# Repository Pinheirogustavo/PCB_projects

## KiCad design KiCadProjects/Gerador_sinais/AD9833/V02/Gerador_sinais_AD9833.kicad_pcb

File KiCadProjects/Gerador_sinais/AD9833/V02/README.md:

# Gerador de Sinais

## Descrição Geral do projeto

Sistema que gera um sinal senoidal com controle de amplitude e frequência.

Estágios: Gerador de sinais ( CA@300mV + DC) &rarr; Filtro  passa-alta &rarr; SinA (CA@300mV) &rarr; buffer &rarr;  amplificador não-inversor &rarr; Sin1(CA@300mV-3V).

## Componentes do circuito:

- Arduino nano: controlador do sistema
- AD9833: gerador de sinais confeccionado em módulo. Gera uma onda senoidal de amplitude fixa de 300mA e offset
- Ad828: Amplificador operacional dedicado ao ganho de sinal. 
	>Amplificador 1 é buffer entre o filtro passa-alta e o circuito de ganho.
	>Amplificador 2 é um amplificador não inversor. Vout = (1+pot/R2)*Vin
- X9c10x: potenciometro digital dedicado ao ganho de sinal

## Cuidados a serem tomados

Para a comunicação SPI, o dispositivo a ser controlado (Chip Select) é selecionado quando o respectivo pino CS está em LOW. Nunca pode-se permitir que dois dispositivos estejam com CS em LOW ao mesmo tempo. Por isso, no programa é preciso garantir que as operações com o AD9833 (select_wave, freq+ e freq-)  após um delay tragam o sinal do CS(AD9833) para LOW e depois devolvam para HIGH. E que as operações com o X9110X (aumento de R, redução de R, guardar R) após um delay tragam o sinal do CS(X9c10X) para LOW e depois devolvam para HIGH.

Assim, primeiramente o programa deve liberar o AD9833 (gerador de sinais) para ocupar a comunicação SPI, após a geração de sinal, desligar sua comunicação (trazer seu CS para HIGH) e liberar a comunicação SPI para ser requisitada a partir dos botões referentes a cada dispositivo. 

## Estágios do circuito

#### Entradas e saídas digitais do arduino nano:

>D2:  cs (X9X104) - Saída digital. Sinal de Chip Select do potenciômetro digital - "The device is selected when the CS input is LOW." 

>D3: storage_R - Usado para armazenar o valor de resistência - Botão 4 - Pressionar o botão faz o sinal X9c10x_INC  ficar em HIGH e o sinal  cs(X9X104) passar de HIGH para LOW e retornar a HIGH

>D4:  cs (AD9833) - Sinal de Chip Select do gerador de sinais

>D5:  Up_pot - Aumenta a resistência do potenciômetro (aumenta o ganho do sistema) - Botão 5 - Pressionar o botão faz com que o sinal de cs(X9X104) passe de HIGH para LOW, que o sinal X9c10x_INC altere de HIGH para LOW e o sinal  X9c10x_U/D fique em HIGH. Ao liberar o botão, o sinal de cs(X9X104) deve retornar para HIGH.
	 
>D6:  Down_pot - Reduz a resistência do potenciômetro (reduz o ganho do sistema) - Botão 6 - Pressionar o botão faz com que o sinal de cs(X9X104) passe de HIGH para LOW, X9c10x_INC altere de HIGH para LOW e o sinal  X9c10x_U/D fique em LOW. Ao liberar o botão, o sinal de cs(X9X104) deve retornar para HIGH.

>D7:  X9c10x_INC - Saída digital. Responsável pelo disparo do sinal que habilita o incremento e o decremento da resistência. Alterado pelos sinais em Up_pot/Down_pot.

>D8:  X9c10x_U/D -  Saída digital. Responsável pela seleção do sinal de incremento ou decremento da resistência. Controlado pelos sinais em Up_pot/Down_pot.

>D9:  freq+   - Incrementa a frequência do sinal (a definir o tamanho do incremento) - Botão 2 - Ainda não implementado no programa.

>D10: freq-   - Decrementa a frequência do sinal (a definir o tamanho do decremento) - Botão 3 - Ainda não implementado no programa.

>D11: SPI_COPI - Saída digital. Sinal de controle do arduino para a entrada SDATA do gerador de sinais.

>D12: S_wave - Seleciona a forma de onda desejada (seno, triangular ou quadrada) - Botão 1 - Ainda não implementado no programa.

>D13: SPI_clk - Saída digital. Sinal de clock entre o arduino e o gerador de sinais

#### O potenciômetro digital

- Programa baseado em: https://www.electroniclinic.com/digital-potentiometer-x9c103s-arduino-circuit-and-programming/

- Pin Descriptions - X9c10x:

#### O Gerador de sinais

- Programa baseado em: https://www.electroniclinic.com/ad9833-programmable-waveform-generator-using-arduino/
- Biblioteca necessária: https://github.com/Billwilliams1952/AD9833-Library-Arduino

## Esquemático

## PCB

## PCB-3D

## PCB Máscara

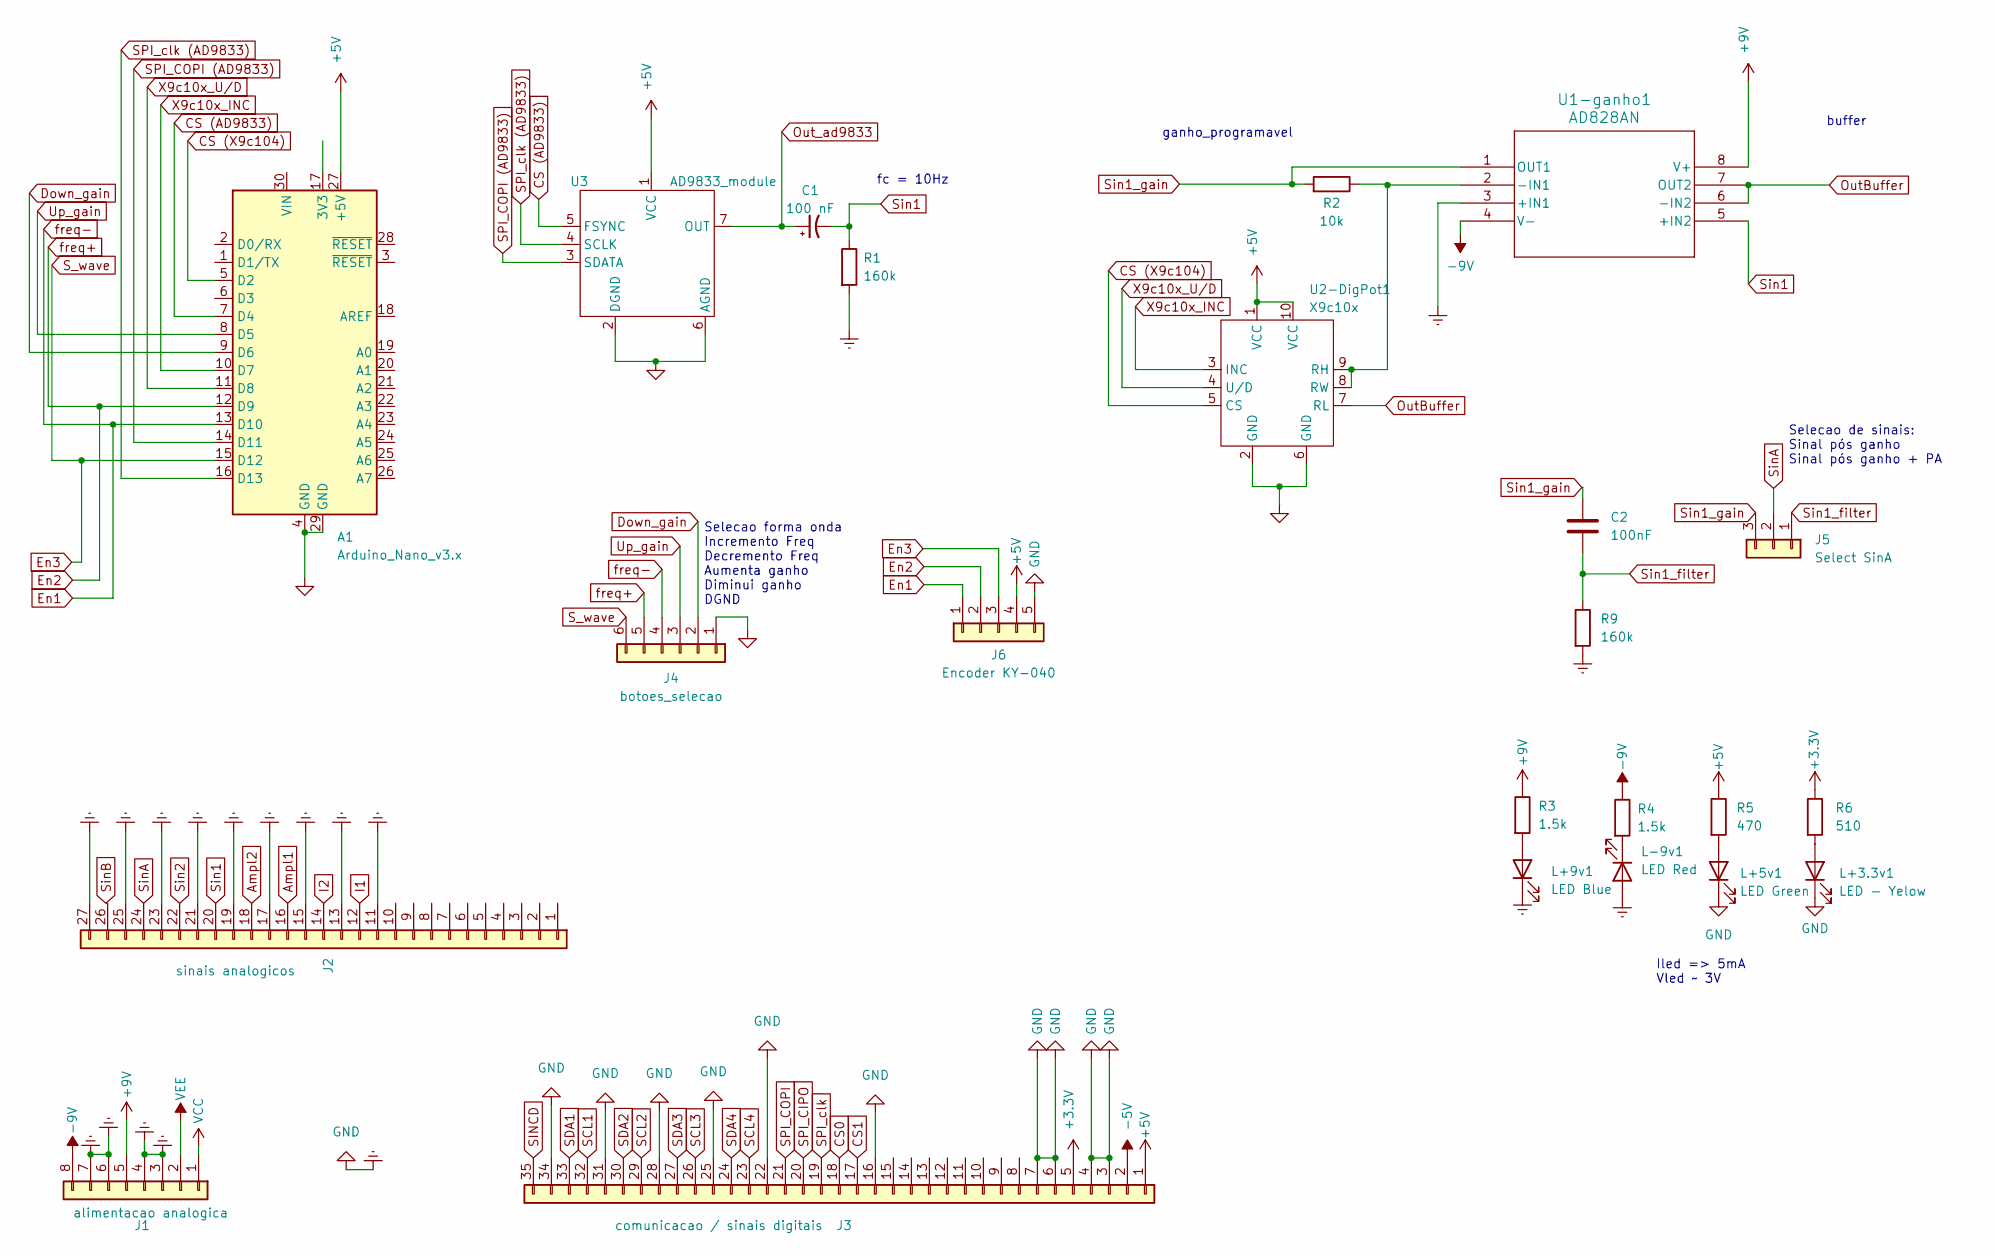
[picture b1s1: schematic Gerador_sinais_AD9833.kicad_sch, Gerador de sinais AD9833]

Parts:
A1: Arduino_Nano_v3.x; Arduino_Nano
C1: 100 nF; CP_Radial_D5.0mm_P2.50mm
C2: 100nF; C_Disc_D3.0mm_W1.6mm_P2.50mm
J1: alimentacao analogica; PinHeader_1x08_P2.54mm_Vertical
J2: sinais analogicos; PinHeader_1x27_P2.54mm_Vertical
J3: comunicacao / sinais digitais; PinHeader_1x35_P2.54mm_Vertical
J4: botoes_selecao; PinHeader_1x06_P2.54mm_Vertical
J5: Select SinA; PinHeader_1x03_P2.54mm_Vertical
J6: Encoder KY-040; PinHeader_1x05_P2.54mm_Vertical
L+3.3v1: LED - Yelow; LED_D5.0mm
L+5v1: LED Green; LED_D5.0mm
L+9v1: LED Blue; LED_D5.0mm
L-9v1: LED Red; LED_D5.0mm
R1: 160k; R_Axial_DIN0204_L3.6mm_D1.6mm_P5.08mm_Horizontal
R2: 10k; R_Axial_DIN0207_L6.3mm_D2.5mm_P7.62mm_Horizontal
R3, R4: 1.5k; R_Axial_DIN0207_L6.3mm_D2.5mm_P7.62mm_Horizontal
R5: 470; R_Axial_DIN0207_L6.3mm_D2.5mm_P7.62mm_Horizontal
R6: 510; R_Axial_DIN0207_L6.3mm_D2.5mm_P7.62mm_Horizontal
R9: 160k; R_Axial_DIN0207_L6.3mm_D2.5mm_P7.62mm_Horizontal
U1-ganho1: AD828AN; AD828
U2-DigPot1: X9c10x; X9c10X_module
U3: AD9833_module

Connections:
+3.3V: J3.5, R6.1
+5V: A1.27 (+5V), J3.1, J6.4, R5.1, U2-DigPot1.1 (VCC), U2-DigPot1.10 (VCC), U3.1 (VCC)
+9V: J1.5, R3.1, U1-ganho1.8 (V+)
-5V: J3.2
-9V: J1.8, R4.1, U1-ganho1.4 (V-)
Ampl1: J2.16
Ampl2: J2.18
CS0: J3.18
CS1: J3.17
CS (AD9833): A1.7 (D4), U3.5 (FSYNC)
CS (X9c104): A1.5 (D2), U2-DigPot1.5 (CS)
Down_gain: A1.9 (D6), J4.2
Earth: A1.4 (GND), A1.29 (GND), J1.3, J1.4, J1.6, J1.7, J2.11, J2.13, J2.15, J2.17, J2.19, J2.21, J2.23, J2.25, J2.27, J3.3, J3.4, J3.6, J3.7, J3.16, J3.22, J3.25, J3.28, J3.31, J3.34, J4.1, J6.5, L+3.3v1.1 (K), L+5v1.1 (K), L+9v1.1 (K), L-9v1.2 (A), R1.2, R9.2, U1-ganho1.3 (+IN1), U2-DigPot1.2 (GND), U2-DigPot1.6 (GND), U3.2 (DGND), U3.6 (AGND)
En1: A1.13 (D10), J4.4, J6.1
En2: A1.12 (D9), J4.5, J6.2
En3: A1.15 (D12), J4.6, J6.3
I1: J2.12
I2: J2.14
unnamed: L+3.3v1.2 (A), R6.2
unnamed: L+5v1.2 (A), R5.2
unnamed: L+9v1.2 (A), R3.2
unnamed: L-9v1.1 (K), R4.2
unnamed: R2.1, U1-ganho1.2 (-IN1), U2-DigPot1.8 (RW), U2-DigPot1.9 (RH)
OutBuffer: U1-ganho1.6 (-IN2), U1-ganho1.7 (OUT2), U2-DigPot1.7 (RL)
Out_ad9833: C1.1, U3.7 (OUT)
SCL1: J3.32
SCL2: J3.29
SCL3: J3.26
SCL4: J3.23
SDA1: J3.33
SDA2: J3.30
SDA3: J3.27
SDA4: J3.24
SINCD: J3.35
SPI_CIPO: J3.20
SPI_COPI: J3.21
SPI_COPI (AD9833): A1.14 (D11), U3.3 (SDATA)
SPI_clk: J3.19
SPI_clk (AD9833): A1.16 (D13), U3.4 (SCLK)
Sin1: C1.2, J2.20, R1.1, U1-ganho1.5 (+IN2)
Sin1_filter: C2.2, J5.1, R9.1
Sin1_gain: C2.1, J5.3, R2.2, U1-ganho1.1 (OUT1)
Sin2: J2.22
SinA: J2.24, J5.2
SinB: J2.26
Up_gain: A1.8 (D5), J4.3
VCC: J1.1
VEE: J1.2
X9c10x_INC: A1.10 (D7), U2-DigPot1.3 (INC)
X9c10x_U/D: A1.11 (D8), U2-DigPot1.4 (U/D)

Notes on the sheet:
ganho_programavel
Selecao forma onda Incremento Freq Decremento Freq Aumenta ganho Diminui ganho DGND
Iled => 5mA Vled ~ 3V
Selecao de sinais: Sinal pós ganho Sinal pós ganho + PA
fc = 10Hz
buffer

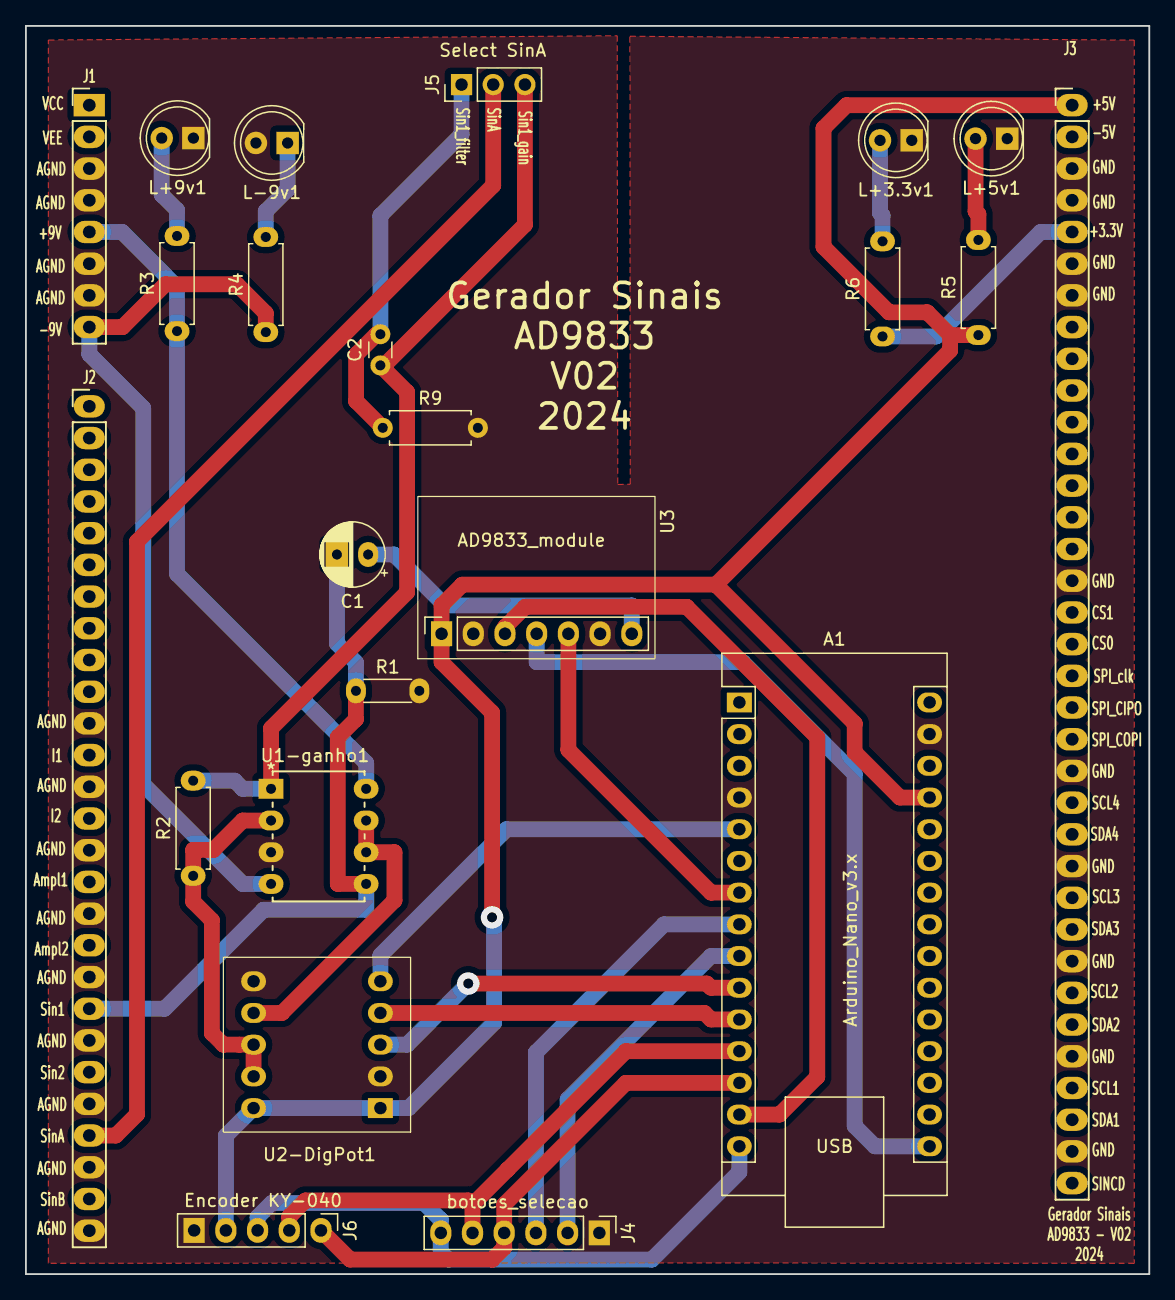
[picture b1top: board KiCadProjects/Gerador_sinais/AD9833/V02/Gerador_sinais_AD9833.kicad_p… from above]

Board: 2 copper layers, 90.0 x 100.0 mm, 23 parts (0 on the bottom side), 27 nets.

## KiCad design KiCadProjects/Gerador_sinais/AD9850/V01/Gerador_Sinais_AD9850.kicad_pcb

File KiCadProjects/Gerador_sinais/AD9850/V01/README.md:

# Gerador de Sinais

## Descrição Geral do projeto

O gerador de sinais é baseado no AD9850. São gerados dois sinais senoidais e dois sinais quadrados, com banda de frequência entre 1 Hz e 40 MHz.

 - Sinais Senoidais: Controle de amplitude e frequência;
 - Sinais quadrados: Controle de frquência.

## Descrição do sistema

#### Gerador de sinais AD9850

O gerador é controlado por quatro sinais digitais vindos do uC STM32. Sua alimentação é feita pelo barramento principal com 5V.

Os sinais quadrados SQ_AD1 e SQ_AD2 passam por um filtro passivo de primeira ordem passa alta, com frequência de corte de 10 Hz. Esses sinais ficam disponíveis na barra de pinos "Squad_wave" como SQ1 e SQ2.

Os sinais senoidais sin_AD1 e sin_AD2 passam por um filtro passivo de primeira ordem passa alta, com frequência de corte de 10 Hz. Esses sinais ficam disponíveis no barramento principal  como Sin1 e Sin2.

#### Circuito de ganho

Os sinais Sin1 e Sin2 entram em um Amplificador Inversor, com o resistor de entrada sendo um potenciômetro digital X9c10x e o resistor de feedback de 51k. O amplificador usado é o AD826/828. 

O controle de cada potenciômetro digital é feito por três sinais digitais vindos do uC STM32. Sua alimentação é feita pelo barramento principal com 5V.

Os sinais Sin1 e Sin2, após passarem por esse estágio de ganho, são nomeados por Sin1_gain e Sin2_gain, respectivamente.

#### Filtro pós ganho

Em simulações realizadas foi observado offset nos sinais após a realização do ganho. Por esse motivo, foi adicionado um estágio, opcional, de filtro Passa-Alta e buffer. Os sinais Sin1_gain e Sin2_gain entram nesse estágio e saem nomeados como Sin1_filter e Sin2_filter

#### Seleção dos sinais para SinA e SinB

O barramento principal do Eitduino recebe os sinais SinA e SinB. Estes podem ser selecionados a partir de  Sin_gain ou Sin_filter por meio de pinos "Select_SinA" e "Select_sinB".

#### Opções de controle por entradas digitais

###### Botões

Quatro botões podem ser implementados para controle de frequência e amplitude do sinal senoidal. Eles são conectados a entradas digitais do uC STM32 (que devem ser definidas como pullup).

###### Teclado matricial

Um teclado matricial 4x4 pode ser implementado para realizar os controles de  frequência e amplitude do sinal senoidal. Esses modelos de teclados numéricos geralmente possuem resistores pullup internos.

###### Encoder

Um encoder pode ser implementado para realizar os controles de  frequência e amplitude do sinal senoidal, em conjunto com os sinais vindos dos botões ou do teclado matricial. Um modelo de fácil acesso é o KY-040, de 20 steps por revolução.

## Descrição do esquemático

###### A1 - Squad Wave

Componentes para filtrar e disponibilisar os dois sinais quadrados.

 > Os sinais quadrados que saem do AD9850, SQ_AD1 e SQ_AD2, passam por um filtro PA e saem como SQ1 e SQ2.
 > SQ1 e SQ2 ficam disponíveis em uma barra de pinos (Squad_wave) junto com o AGND.

###### A2 - Encoder

Barra de pinos (encoder ky-040) para encaixe do módulo encoder como o KY-040. 

 > O módulo encoder trabalha com cinco pinos. +5V e DNGD para alimentação. Os outros três pinos são sinais digitais (En1, En2 e En3) que enviam dados para o uC.
 
 As conexões entre o encoder e o uC são:
 
	En1       PA15
	En2       PB8
	En3       PB9

###### A3 - Teclado matricial

Barra de pinos (teclado matricial) para conexão do teclado matricial 4x4.

 > São oito pinos de sinais digitais (M1, M2, ... , M8) que enviam dados para o uC.

As conexões entre o teclado e o uC são:

	M1        PA2
	M2        PA3
	M3        PA12
	M4        PA11
	M5        PA6
	M6        PA7
	M7        PB0
	M8        PB12

###### A4 - botões

Barra de pinos (botoes_selecao) para conexão de 4 botões.

 > São quatro pinos para conexão de botões e um pino DGND. Os quatro pinos dos botões são:
 
	Freq +: incrementa a frequência dos sinais gerados
	Freq -: decrementa a frequência dos sinais gerados
	Up_gain: incrementa a amplitude dos sinais gerados
	Down_gain: decrementa a amplitude dos sinais gerados
    
As conexões entre os botoes e o uC são:

	Freq+         PB13
	Freq-         PB14
	Up_gain       PB15
	Down_gain     PA8
    
 > Os botões devem ser conectados ao sinal DGND presente na barra de pinos  e nas entradas digitais do uC. Essas entradas devem estar definidas com pullup. 

###### B1 - AD9850

Modelo de componente criado nas dimensões do módulo utilizado.

As conexões entre o módulo e o uC são:

	W_CLK     PC14
	FQ_UD     PC15
	DATA      PA0
	RESET     PA1
    
Os sinais senoidais (com offset) fornecidos são: sin_AD1 e sin_AD2

A alimentação é feita por: +5V e DGND

###### C1 - Filtro saída AD9850

###### B2 - uC STM32

Alimentação: pode ser feita por 3.3V ou 5.0V - jumper na barra de pinos (3.3V STM32 **OU** 5.0V STM32).

Entradas Digitais: Ver "Encoder", "Teclado matricial" e "Botões".

Saídas digitais: Ver "AD9850" e "DigPot1 / DigPot2" em "Ganho programável".

Entradas Analógicas:

	PA4       Ampl1 (amplitude da corrente I1 - vinda do barramento principal)
	PA5       Ampl2 (amplitude da corrente I2 - vinda do barramento principal)

Comunicação I2C: O uC está conectado ao barramento principal de comunicação I2C-1. No primeiro momento essa funcionalidade não é utilizada, mas foi implementada caso optemos por realizar o controle do sinal de excitação por outro uC de outro módulo do projeto. 
Há resistores pullup (+3.3V) para essa comunicação.

###### C1 e D1 - Barramento principal

Verificar os sinais dispo no barramento principal em: <https://github.com/Pinheirogustavo/PCB_projects>

###### C3 - LEDs de alimentação

LEDs de diferentes cores para indicar o correto fornecimento das tensões empregadas no circuito.

Foi considerado uma tensão de joelho de aproximadamente 3V e uma corrente de 5mA para ter o um brilho perceptível e baixo consumo de energia.

 - Azul:        +9V
 - Vermelho:    -9V
 - Verde:       +5V
 - Amarelo:     +3.3V

###### A5 e B5 - Ganho programável

Amplificador duplo (AD826/828) na forma não inversor para controle do ganho do sinal senoidal filtrado vindo do AD9850.

Cada um dos sinais (Sin1 e Sin2) passa por um potenciômetro digital diferente (DIgPot 1 e DigPot2). Ambos estão conectados à entrada não inversora do amplificador. 

Cada potenciômetro digital (DigPot) possui um vetor resistivo de 99 passos. O CI X9c104 possui resistência máxima de $100k \Omega$. Ele é controlado por 4 sinais digitais.

As conexões entre os potenciômetros digitais e o uC são:

	Pot1_CS_(X9c104)      PB1
	Pot1_X9c10x_U/D       PB10
	Pot1_X9c10x_INC       PB11

	Pot2_CS_(X9c104)      PB5
	Pot2_X9c10x_U/D       PB4 
	Pot2_X9c10x_INC       PB3 

###### C5 - Filtro e buffer

## Particularidades na construção da PCB

Devido o tamanho restrito da placa e o grande número de componentes, foram adotados tamanhos de trilha e espaçamentos diferentes dos padrões.

 - Tamanho de trilha: 0,50mm
 - Espaçamento: 0,50mm
 - Tamnho de via: 1,00mm furo da via: 0,60mm
 - Pads:
 	- Resistor: circular 1,6mm furo 0,8mm
 	- capacitor: oval 1,8x2,0mm furo 1,1mm
 	- Barra de pinos (excerto principais): oval 1,8x2,0mm furo 1,02mm
 	- AmpOp: circular 1,6mm furo 0,8mm

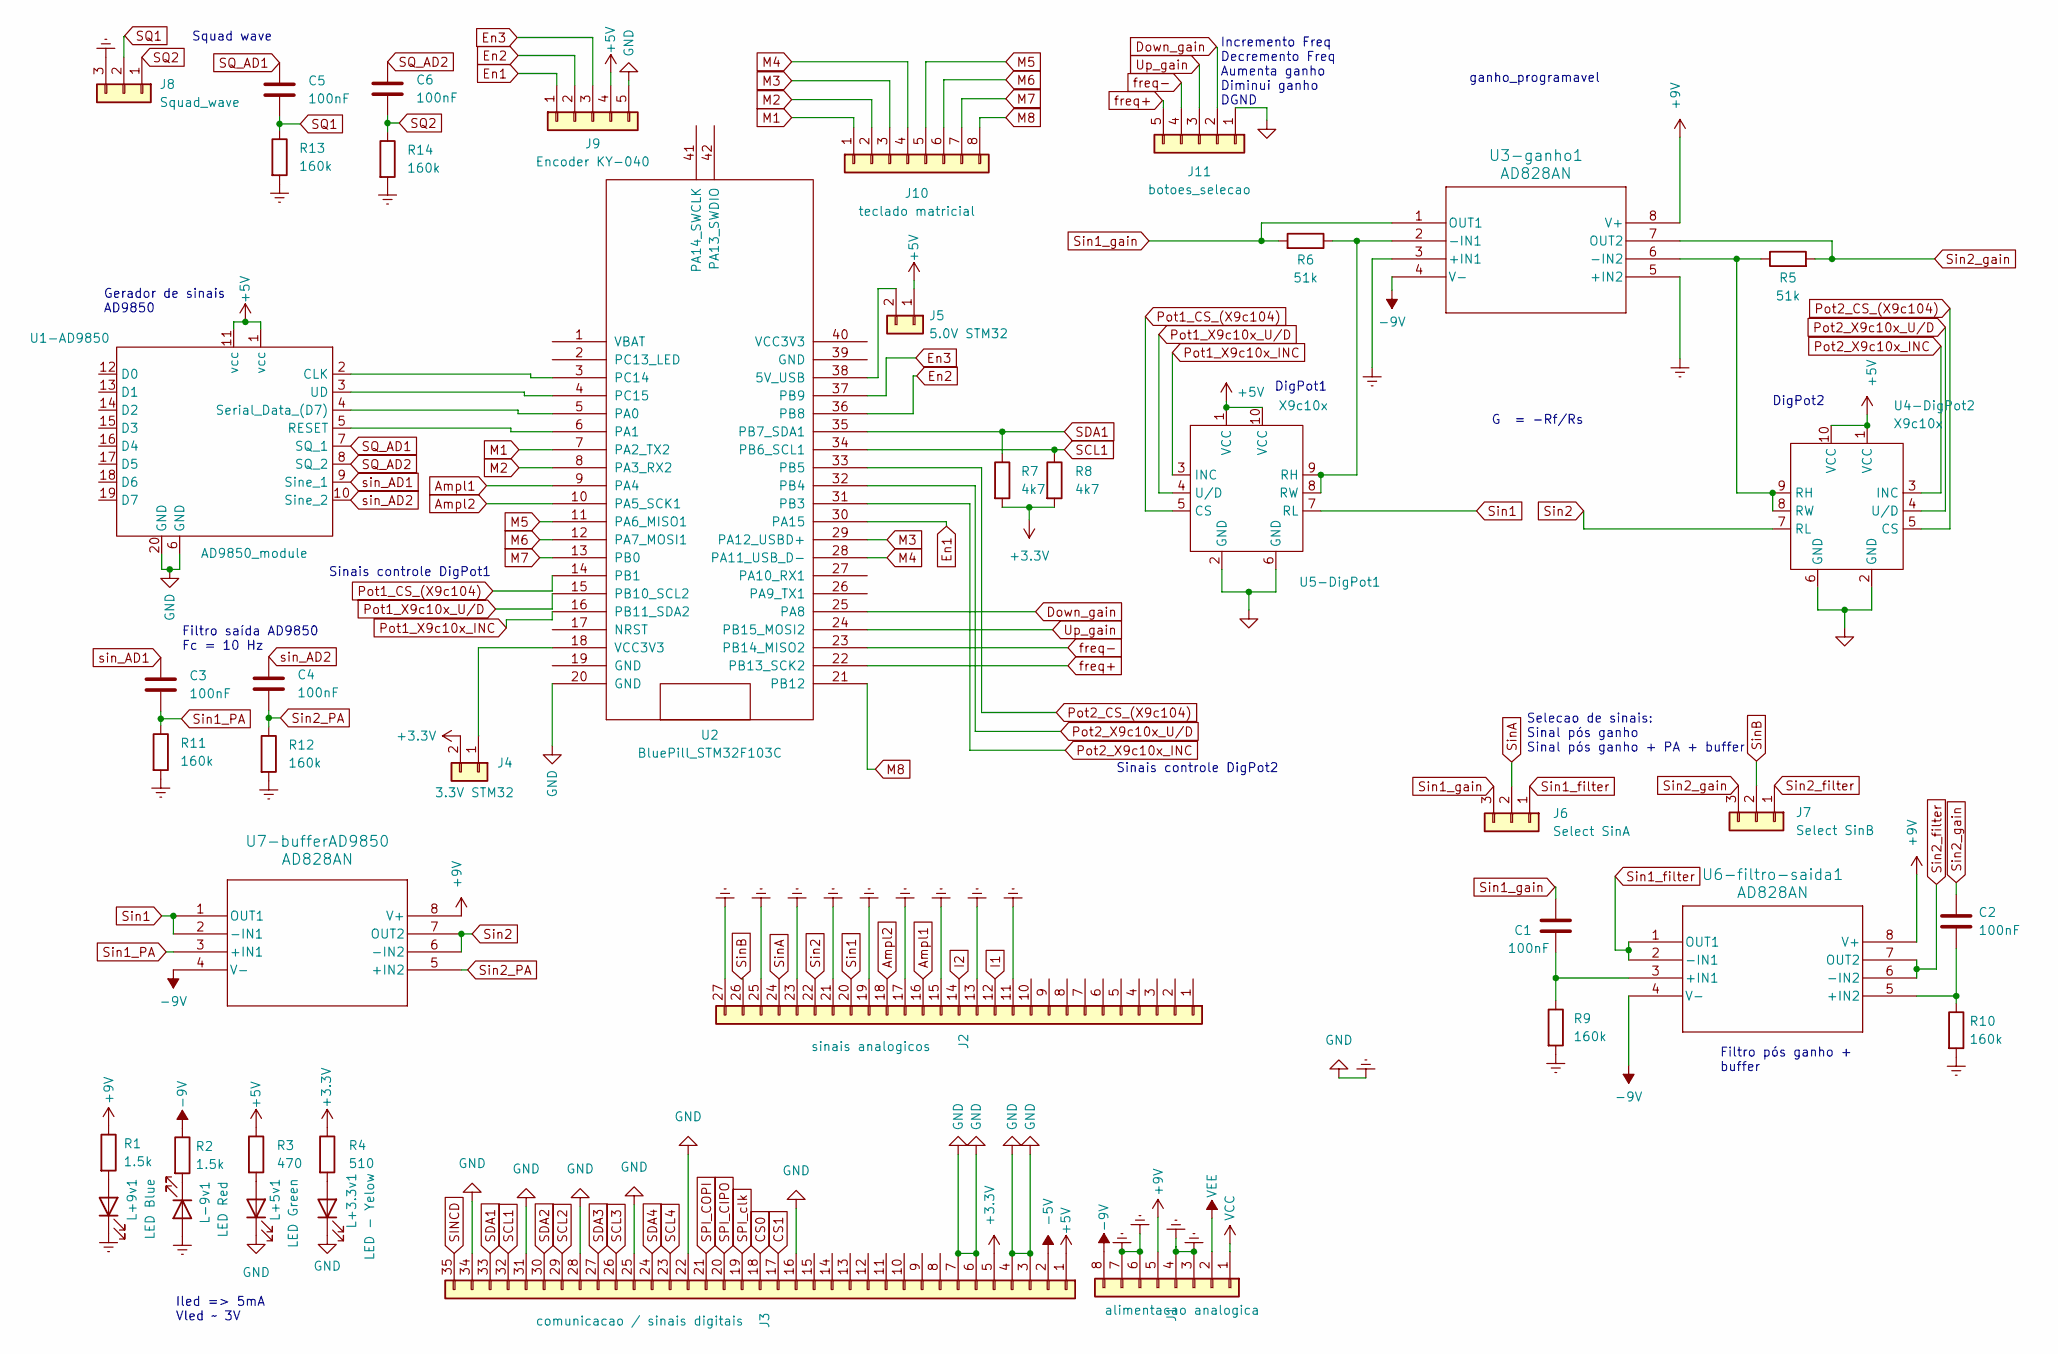
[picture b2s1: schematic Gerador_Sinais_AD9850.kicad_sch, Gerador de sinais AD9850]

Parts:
C1, C2, C3, C4, C5, C6: 100nF; C_Disc_D3.0mm_W1.6mm_P2.50mm
J1: alimentacao analogica; PinHeader_1x08_P2.54mm_Vertical
J2: sinais analogicos; PinHeader_1x27_P2.54mm_Vertical
J3: comunicacao / sinais digitais; PinHeader_1x35_P2.54mm_Vertical
J4: 3.3V STM32; PinHeader_1x02_P2.54mm_Vertical
J5: 5.0V STM32; PinHeader_1x02_P2.54mm_Vertical
J6: Select SinA; PinHeader_1x03_P2.54mm_Vertical
J7: Select SinB; PinHeader_1x03_P2.54mm_Vertical
J8: Squad_wave; PinHeader_1x03_P2.54mm_Vertical
J9: Encoder KY-040; PinHeader_1x05_P2.54mm_Vertical
J10: teclado matricial; PinHeader_1x08_P2.54mm_Horizontal
J11: botoes_selecao; PinHeader_1x05_P2.54mm_Horizontal
L+3.3v1: LED - Yelow; LED_D5.0mm
L+5v1: LED Green; LED_D5.0mm
L+9v1: LED Blue; LED_D5.0mm
L-9v1: LED Red; LED_D5.0mm
R1, R2: 1.5k; R_Axial_DIN0207_L6.3mm_D2.5mm_P7.62mm_Horizontal
R3: 470; R_Axial_DIN0207_L6.3mm_D2.5mm_P7.62mm_Horizontal
R4: 510; R_Axial_DIN0207_L6.3mm_D2.5mm_P7.62mm_Horizontal
R5, R6: 51k; R_Axial_DIN0207_L6.3mm_D2.5mm_P7.62mm_Horizontal
R7, R8: 4k7; R_Axial_DIN0207_L6.3mm_D2.5mm_P7.62mm_Horizontal
R9, R10, R11, R12, R13, R14: 160k; R_Axial_DIN0207_L6.3mm_D2.5mm_P7.62mm_Horizontal
U1-AD9850: AD9850_module
U2: BluePill_STM32F103C
U3-ganho1, U6-filtro-saida1, U7-bufferAD9850: AD828AN; AD828
U4-DigPot2, U5-DigPot1: X9c10x; X9c10X_module

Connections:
+3.3V: J3.5, J4.2, R4.1, R7.2, R8.2
+5V: J3.1, J5.1, J9.4, R3.1, U1-AD9850.1 (vcc), U1-AD9850.11 (vcc), U4-DigPot2.1 (VCC), U4-DigPot2.10 (VCC), U5-DigPot1.1 (VCC), U5-DigPot1.10 (VCC)
+9V: J1.5, R1.1, U3-ganho1.8 (V+), U6-filtro-saida1.8 (V+), U7-bufferAD9850.8 (V+)
-5V: J3.2
-9V: J1.8, R2.1, U3-ganho1.4 (V-), U6-filtro-saida1.4 (V-), U7-bufferAD9850.4 (V-)
Ampl1: J2.16, U2.9 (PA4)
Ampl2: J2.18, U2.10 (PA5_SCK1)
CS0: J3.18
CS1: J3.17
Down_gain: J11.2, U2.25 (PA8)
Earth: J1.3, J1.4, J1.6, J1.7, J2.11, J2.13, J2.15, J2.17, J2.19, J2.21, J2.23, J2.25, J2.27, J3.3, J3.4, J3.6, J3.7, J3.16, J3.22, J3.25, J3.28, J3.31, J3.34, J8.3, J9.5, J11.1, L+3.3v1.1 (K), L+5v1.1 (K), L+9v1.1 (K), L-9v1.2 (A), R9.2, R10.2, R11.2, R12.2, R13.2, R14.2, U1-AD9850.6 (GND), U1-AD9850.20 (GND), U2.20 (GND), U3-ganho1.3 (+IN1), U3-ganho1.5 (+IN2), U4-DigPot2.2 (GND), U4-DigPot2.6 (GND), U5-DigPot1.2 (GND), U5-DigPot1.6 (GND)
En1: J9.1, U2.30 (PA15)
En2: J9.2, U2.36 (PB8)
En3: J9.3, U2.37 (PB9)
I1: J2.12
I2: J2.14
M1: J10.1, U2.7 (PA2_TX2)
M2: J10.2, U2.8 (PA3_RX2)
M3: J10.3, U2.29 (PA12_USBD+)
M4: J10.4, U2.28 (PA11_USB_D-)
M5: J10.5, U2.11 (PA6_MISO1)
M6: J10.6, U2.12 (PA7_MOSI1)
M7: J10.7, U2.13 (PB0)
M8: J10.8, U2.21 (PB12)
unnamed: J4.1, U2.18 (VCC3V3)
unnamed: J5.2, U2.38 (5V_USB)
unnamed: L+3.3v1.2 (A), R4.2
unnamed: L+5v1.2 (A), R3.2
unnamed: L+9v1.2 (A), R1.2
unnamed: L-9v1.1 (K), R2.2
unnamed: U1-AD9850.2 (CLK), U2.3 (PC14)
unnamed: U1-AD9850.5 (RESET), U2.6 (PA1)
unnamed: U1-AD9850.4 (Serial_Data_(D7)), U2.5 (PA0)
unnamed: U1-AD9850.3 (UD), U2.4 (PC15)
unnamed: R6.1, U3-ganho1.2 (-IN1), U5-DigPot1.8 (RW), U5-DigPot1.9 (RH)
unnamed: R5.1, U3-ganho1.6 (-IN2), U4-DigPot2.8 (RW), U4-DigPot2.9 (RH)
unnamed: C1.2, R9.1, U6-filtro-saida1.3 (+IN1)
unnamed: C2.2, R10.1, U6-filtro-saida1.5 (+IN2)
Pot1_CS_(X9c104): U2.14 (PB1), U5-DigPot1.5 (CS)
Pot1_X9c10x_INC: U2.16 (PB11_SDA2), U5-DigPot1.3 (INC)
Pot1_X9c10x_U/D: U2.15 (PB10_SCL2), U5-DigPot1.4 (U/D)
Pot2_CS_(X9c104): U2.33 (PB5), U4-DigPot2.5 (CS)
Pot2_X9c10x_INC: U2.31 (PB3), U4-DigPot2.3 (INC)
Pot2_X9c10x_U/D: U2.32 (PB4), U4-DigPot2.4 (U/D)
SCL1: J3.32, R8.1, U2.34 (PB6_SCL1)
SCL2: J3.29
SCL3: J3.26
SCL4: J3.23
SDA1: J3.33, R7.1, U2.35 (PB7_SDA1)
SDA2: J3.30
SDA3: J3.27
SDA4: J3.24
SINCD: J3.35
SPI_CIPO: J3.20
SPI_COPI: J3.21
SPI_clk: J3.19
SQ1: C5.2, J8.2, R13.1
SQ2: C6.2, J8.1, R14.1
SQ_AD1: C5.1, U1-AD9850.7 (SQ_1)
SQ_AD2: C6.1, U1-AD9850.8 (SQ_2)
Sin1: J2.20, U5-DigPot1.7 (RL), U7-bufferAD9850.1 (OUT1), U7-bufferAD9850.2 (-IN1)
Sin1_PA: C3.2, R11.1, U7-bufferAD9850.3 (+IN1)
Sin1_filter: J6.1, U6-filtro-saida1.1 (OUT1), U6-filtro-saida1.2 (-IN1)
Sin1_gain: C1.1, J6.3, R6.2, U3-ganho1.1 (OUT1)
Sin2: J2.22, U4-DigPot2.7 (RL), U7-bufferAD9850.6 (-IN2), U7-bufferAD9850.7 (OUT2)
Sin2_PA: C4.2, R12.1, U7-bufferAD9850.5 (+IN2)
Sin2_filter: J7.1, U6-filtro-saida1.6 (-IN2), U6-filtro-saida1.7 (OUT2)
Sin2_gain: C2.1, J7.3, R5.2, U3-ganho1.7 (OUT2)
SinA: J2.24, J6.2
SinB: J2.26, J7.2
Up_gain: J11.3, U2.24 (PB15_MOSI2)
VCC: J1.1
VEE: J1.2
freq+: J11.5, U2.22 (PB13_SCK2)
freq-: J11.4, U2.23 (PB14_MISO2)
sin_AD1: C3.1, U1-AD9850.9 (Sine_1)
sin_AD2: C4.1, U1-AD9850.10 (Sine_2)

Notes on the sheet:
Iled => 5mA Vled ~ 3V
DigPot1
Squad wave
Filtro saída AD9850 Fc = 10 Hz
Filtro pós ganho + buffer
DigPot2
Gerador de sinais AD9850
Sinais controle DigPot2
Incremento Freq Decremento Freq Aumenta ganho Diminui ganho DGND
Selecao de sinais: Sinal pós ganho Sinal pós ganho + PA + buffer
ganho_programavel
Sinais controle DigPot1
G = -Rf/Rs

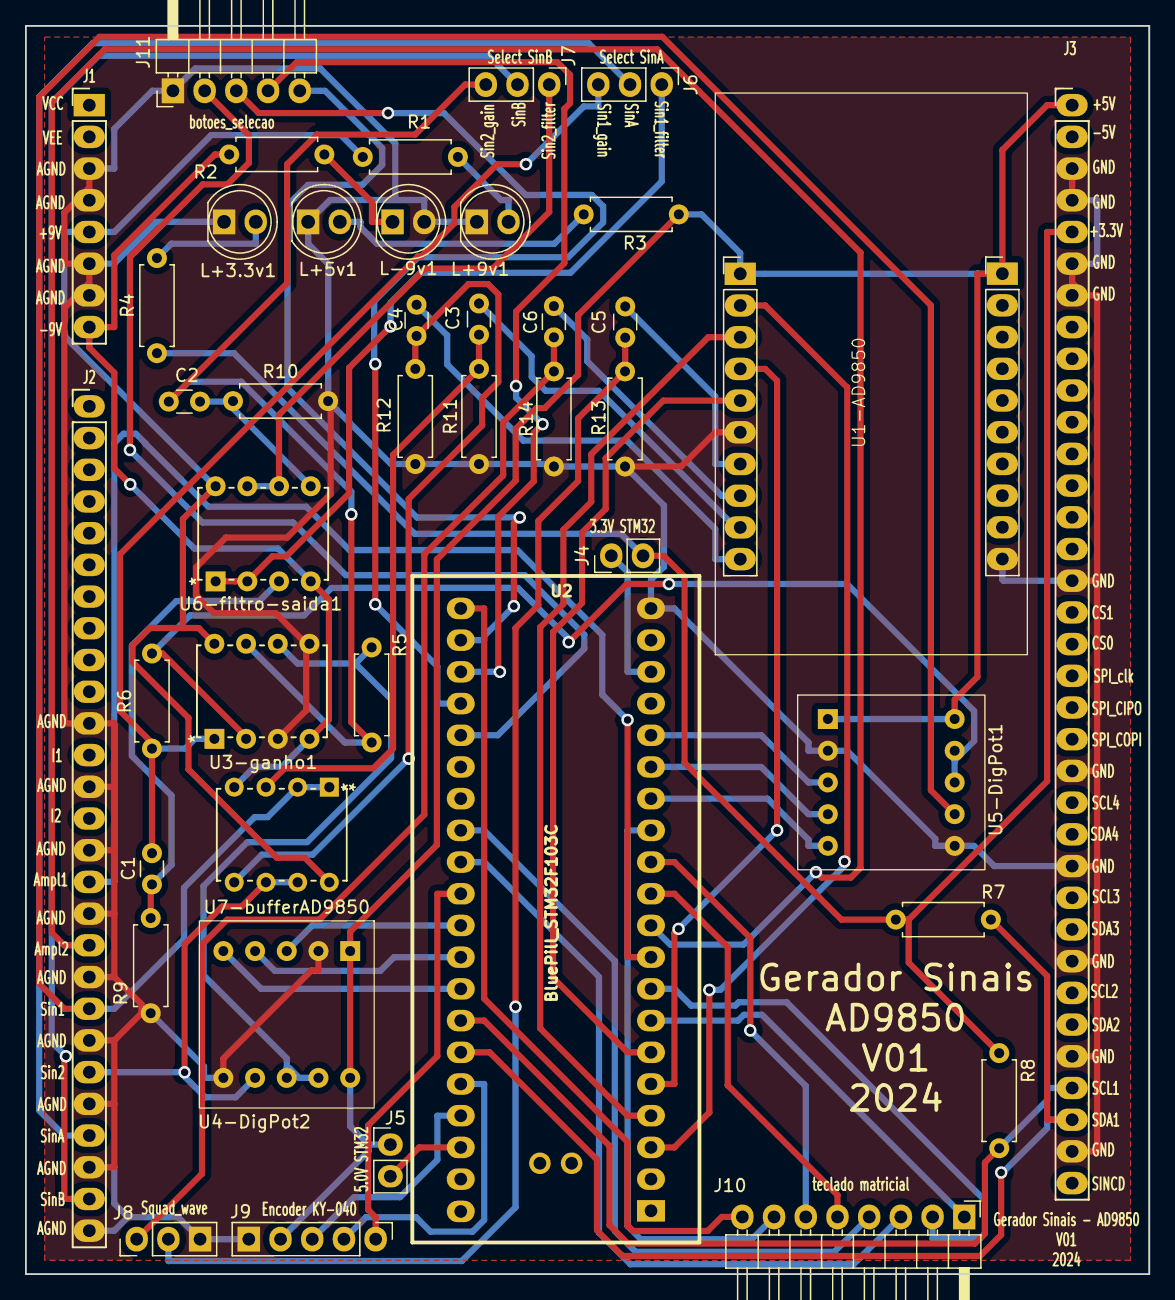
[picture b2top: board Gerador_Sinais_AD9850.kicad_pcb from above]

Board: 2 copper layers, 90.0 x 100.0 mm, 42 parts (0 on the bottom side), 60 nets.

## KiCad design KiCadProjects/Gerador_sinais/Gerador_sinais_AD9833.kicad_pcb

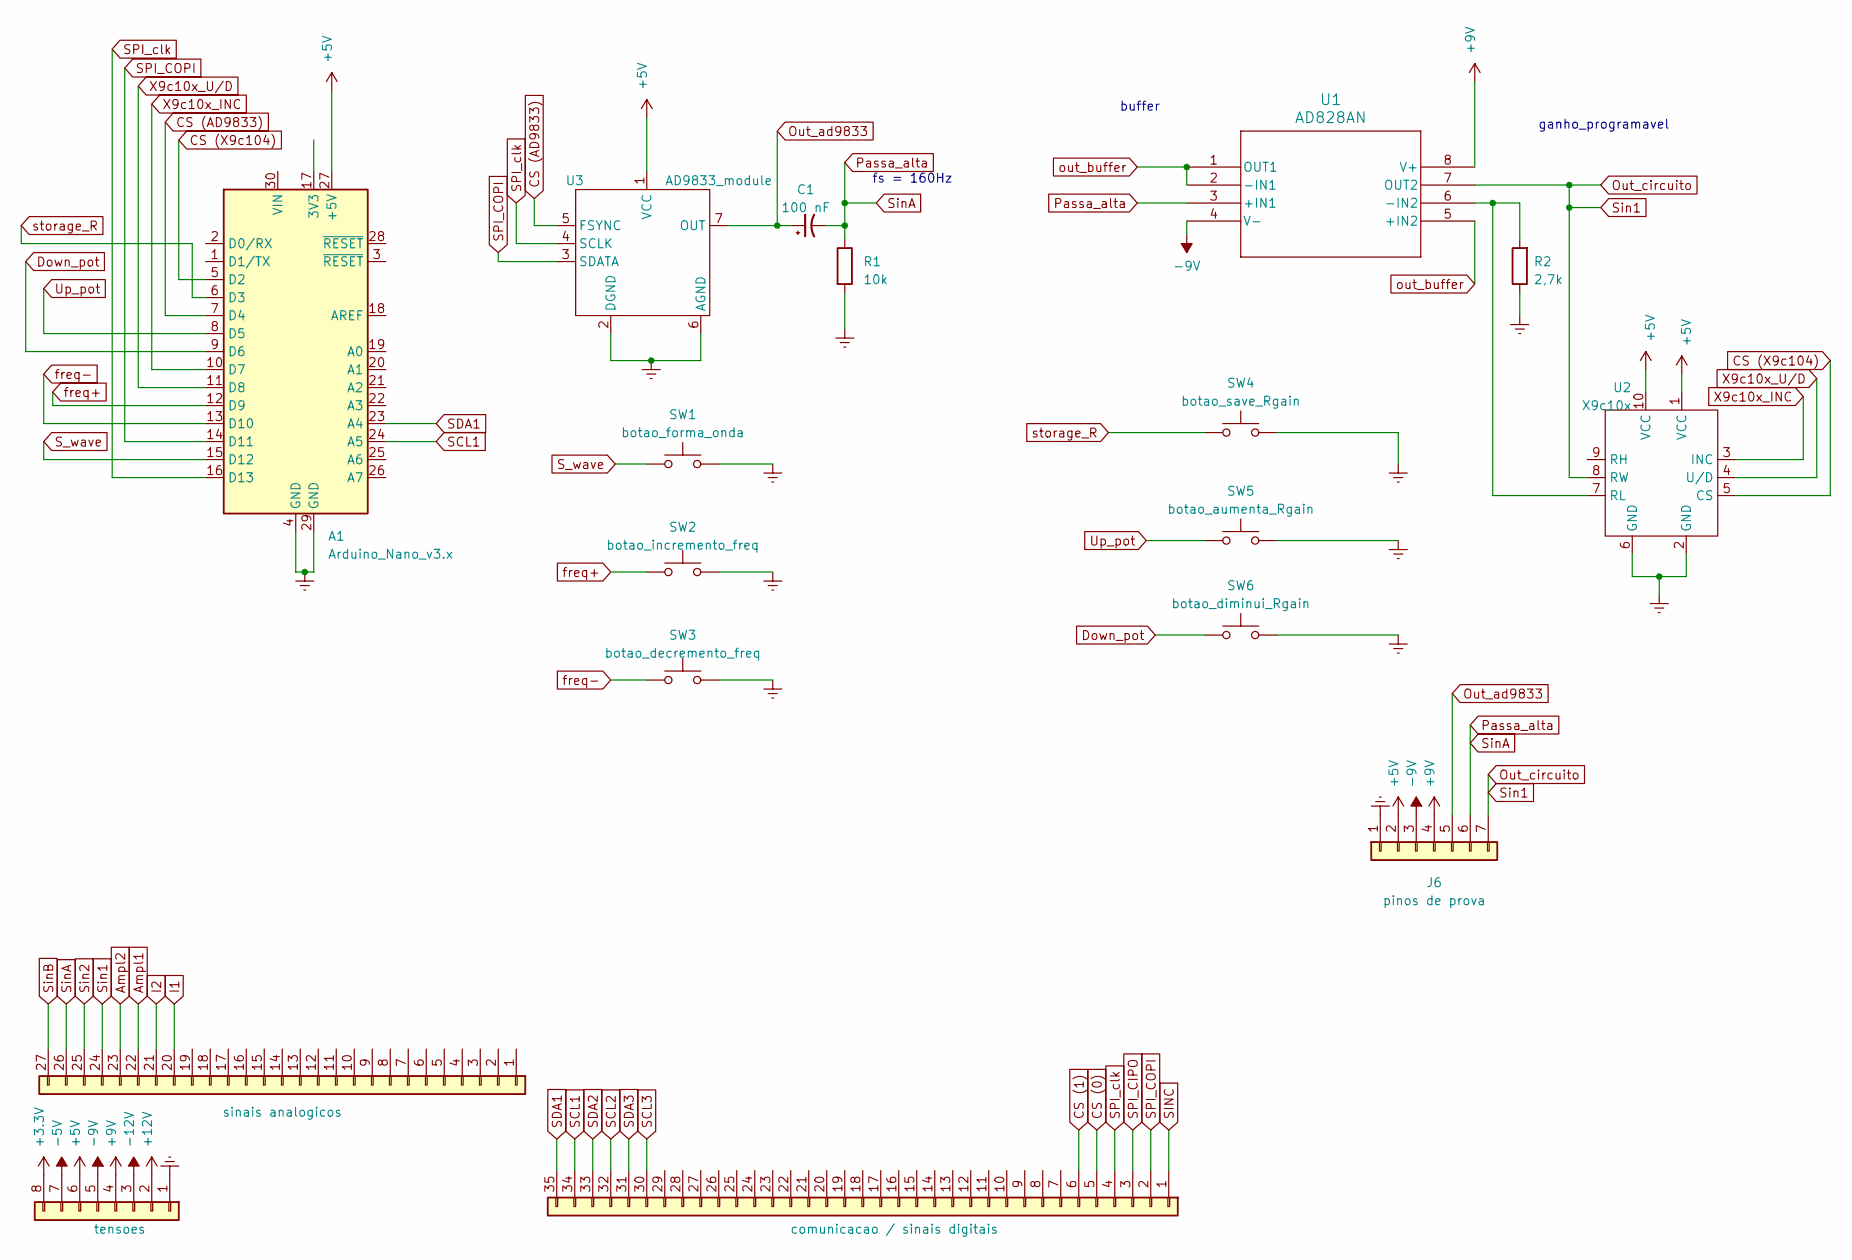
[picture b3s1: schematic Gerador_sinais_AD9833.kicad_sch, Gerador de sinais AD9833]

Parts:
A1: Arduino_Nano_v3.x; Arduino_Nano
C1: 100 nF; CP_Radial_D4.0mm_P1.50mm
J1: tensoes; PinHeader_1x08_P2.54mm_Vertical
J3: sinais analogicos; PinHeader_1x27_P2.54mm_Vertical
J4: comunicacao / sinais digitais; PinHeader_1x35_P2.54mm_Vertical
J6: pinos de prova; PinHeader_1x07_P2.54mm_Horizontal
R1: 10k; R_Axial_DIN0204_L3.6mm_D1.6mm_P5.08mm_Horizontal
R2: 2,7k; R_Axial_DIN0204_L3.6mm_D1.6mm_P5.08mm_Horizontal
SW1: botao_forma_onda; SW_BUTT-2
SW2: botao_incremento_freq; SW_BUTT-2
SW3: botao_decremento_freq; SW_BUTT-2
SW4: botao_save_Rgain; SW_BUTT-2
SW5: botao_aumenta_Rgain; SW_BUTT-2
SW6: botao_diminui_Rgain; SW_BUTT-2
U1: AD828AN; N_8_ADI
U2: X9c10x; X9c10X_module
U3: AD9833_module

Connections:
+3.3V: J1.8
+5V: A1.27 (+5V), J1.6, J6.2, U2.1 (VCC), U2.10 (VCC), U3.1 (VCC)
+9V: J1.4, J6.4, U1.8 (V+)
+12V: J1.2
-5V: J1.7
-9V: J1.5, J6.3, U1.4 (V-)
-12V: J1.3
Ampl1: J3.22
Ampl2: J3.23
CS (0): J4.5
CS (1): J4.6
CS (AD9833): A1.7 (D4), U3.5 (FSYNC)
CS (X9c104): A1.5 (D2), U2.5 (CS)
Down_pot: A1.9 (D6), SW6.1
Earth: A1.4 (GND), A1.29 (GND), J1.1, J6.1, R1.2, R2.1, SW1.2, SW2.2, SW3.2, SW4.2, SW5.2, SW6.2, U2.2 (GND), U2.6 (GND), U3.2 (DGND), U3.6 (AGND)
I1: J3.20
I2: J3.21
unnamed: R2.2, U1.6 (-IN2), U2.7 (RL)
Out_ad9833: C1.1, J6.5, U3.7 (OUT)
Out_circuito: J3.24, J6.7, U1.7 (OUT2), U2.8 (RW)
Passa_alta: C1.2, J3.26, J6.6, R1.1, U1.3 (+IN1)
SCL1: A1.24 (A5), J4.34
SCL2: J4.32
SCL3: J4.30
SDA1: A1.23 (A4), J4.35
SDA2: J4.33
SDA3: J4.31
SINC: J4.1
SPI_CIPO: J4.3
SPI_COPI: A1.14 (D11), J4.2, U3.3 (SDATA)
SPI_clk: A1.16 (D13), J4.4, U3.4 (SCLK)
S_wave: A1.15 (D12), SW1.1
Sin2: J3.25
SinB: J3.27
Up_pot: A1.8 (D5), SW5.1
X9c10x_INC: A1.10 (D7), U2.3 (INC)
X9c10x_U/D: A1.11 (D8), U2.4 (U/D)
freq+: A1.12 (D9), SW2.1
freq-: A1.13 (D10), SW3.1
out_buffer: U1.1 (OUT1), U1.2 (-IN1), U1.5 (+IN2)
storage_R: A1.6 (D3), SW4.1

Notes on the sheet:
ganho_programavel
fs = 160Hz
buffer

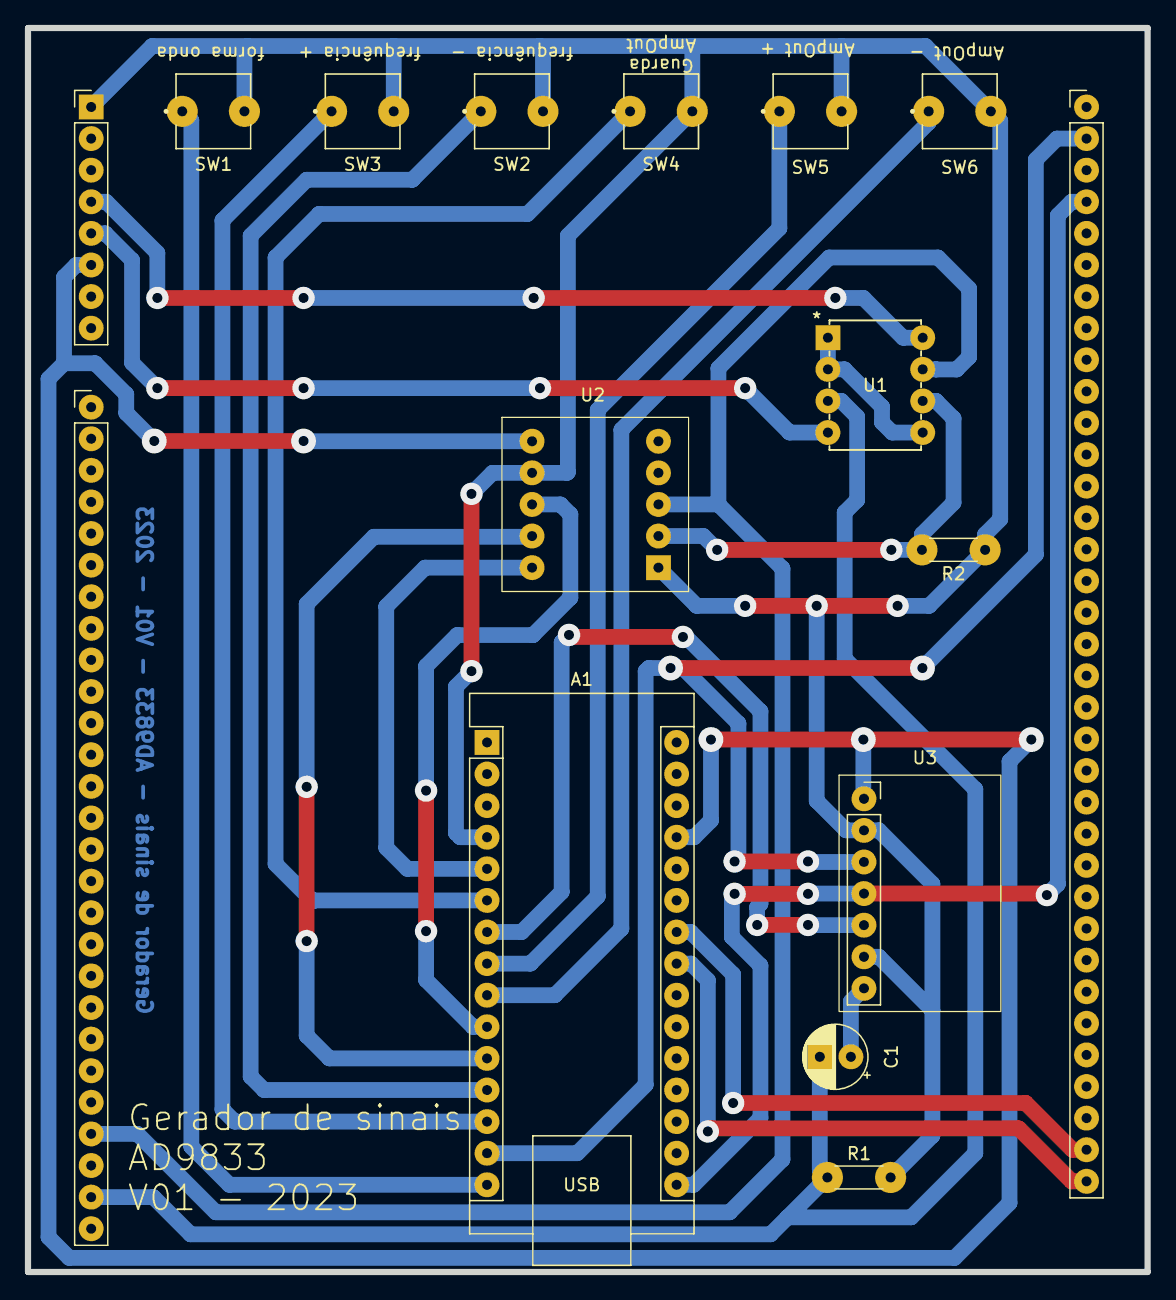
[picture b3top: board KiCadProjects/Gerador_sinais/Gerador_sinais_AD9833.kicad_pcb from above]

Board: 2 copper layers, 90.0 x 100.0 mm, 16 parts (0 on the bottom side), 23 nets.
